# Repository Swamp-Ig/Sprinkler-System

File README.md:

# 6-Zone WiFi Sprinkler Controller

A custom PCB for controlling up to six 24 VAC irrigation solenoid valves via WiFi, using an ESP32 and ESPHome with native Home Assistant integration.

## Features

- **6 independent zones** — each zone switches a 24 VAC solenoid valve via an Omron G5LE-1 relay
- **WiFi control** — ESP32-WROOM-32U with external U.FL antenna connector
- **Home Assistant integration** — ESPHome firmware; zones appear as switch entities
- **Onboard power supply** — HLK-PM01 AC-DC module (mains → 5 V); AMS1117-3.3 regulator (5 V → 3.3 V for ESP32)
- **Relay isolation** — ULN2803A Darlington array isolates ESP32 GPIOs from relay coil drive current
- **Protected design** — varistors on each zone output and across the mains input and transformer primary (RV1/RV2), time-delay fuses on the mains and 24 VAC supplies, per-zone RC snubbers, and an optocoupler-isolated 24 VAC rail sense

## ⚠️ Safety

> **This board carries mains voltage (Line and Neutral) on the PCB.**  
> The HLK-PM01 module is connected directly to mains. The 24 VAC solenoid rail is transformer-isolated but still carries AC voltage.

- Do **not** touch or probe the board while it is powered.
- The enclosure **must** be non-conductive and fully closed before applying mains power.
- All mains wiring must comply with local electrical codes. Use appropriately rated cable and terminals.
- The external transformer must be safety-rated (UL, CE, or equivalent) for your locale.
- Replace fuses only with the specified ratings — see the BOM below.

See [Assembly Notes](docs/assembly.md) for enclosure requirements and conformal coating instructions.

## How It Works

The controller has three linked paths: logic power, 24 VAC valve power, and relay control.

**Logic power:** Mains → F1 → HLK-PM01 → 5 V → AMS1117-3.3 → 3.3 V → ESP32 + logic

**24 VAC path:** Mains → F1 → G3MB-202P SSR (K1, GPIO16) → J2 → external transformer → J3 → F2 → zone relays (K20–K25) → solenoids

**Control:** ESP32 GPIO17–23 → ULN2803A → relay coils K20–K25 → zone outputs J20–J25

When a zone is activated, the ESP32 first enables the 24 VAC rail (K1), then drives the selected relay through the ULN2803A. The ULN2803A acts as a low-side driver, keeping ESP32 GPIO current low while switching the 24 VAC solenoid load through the relay contacts.

## Bill of Materials

| Ref | Component | Value / Part No. | Notes |
|-----|-----------|-----------------|-------|
| U4 | ESP32 module | ESP32-WROOM-32U | External antenna (U.FL) |
| U3 | AC-DC module | HLK-PM01 | 100–240 VAC in, 5 V / 600 mA out |
| U1 | LDO regulator | AMS1117-3.3 | SOT-223 |
| U2 | Optocoupler | EL817 | Isolates the 24 VAC rail sense |
| U5 | Darlington array | ULN2803A | SOIC-18 |
| K1 | Solid-state relay | Omron G3MB-202P | Gates the 24 VAC solenoid rail (GPIO16) |
| K20–K25 | Relay ×6 | Omron G5LE-1 | SPDT, 5 V coil, 10 A / 250 VAC contacts |
| RV20–RV25 | Varistor ×6 | 68 V | Surge protection, one per zone output |
| RV1 | Varistor | 10D471K (275 VAC) | Across mains L–N input, after F1 |
| RV2 | Varistor | 10D471K (275 VAC) | Across K1 SSR output / transformer primary |
| F1 | Fuse | **T1A** (time-delay) | Mains supply — slow-blow for transformer/HLK inrush |
| F2 | Fuse | **T2A** (time-delay) | 24 VAC supply — slow-blow for solenoid inrush |
| D1 | Diode | 1N4148 (0805) | 24 VAC rail sense |
| C5 | Capacitor | 220 µF / ≥10 V | 5 V rail bulk reservoir (THT radial) |
| C1, C7 | SMD capacitors | 10 µF | Supply filtering |
| C2, C3 | SMD capacitors | 22 µF | Supply filtering / sense |
| C4, C6, C20–C25 | SMD capacitors | 100 nF | ESP32 VDD (C4), EN reset (C6), zone snubbers (C20–C25) |
| R1, R3, R5, R6, R8, R10, R11 | SMD resistors | 10 kΩ | Sense, pull-ups, pull-downs |
| R2, R9, R12–R14 | SMD resistors | 4.7 kΩ | Sense, LED series, I²C pull-ups |
| R4, R7 | SMD resistors | 470 Ω | EN/BOOT switch series |
| R20–R25 | SMD resistors | 100 Ω | Zone snubber series |
| LED1, LED2 | LED ×2 | 0805 | IO2 status / power |
| SW1, SW2 | Tactile switch ×2 | — | EN (reset) / BOOT |
| J1 | Screw terminal | Phoenix PT 1,5/3-5.0 (3-pin, 5.0 mm) | Mains input — must be mains-rated |
| J2 | Screw terminal | 2-pin, 5.0 mm | 240 VAC output to transformer primary |
| J3, J20–J25 | Pluggable terminal ×7 | KF2EDG-style, 2-pin | 24 VAC — J3 transformer in, J20–J25 zone outputs |
| XFMR | Transformer (external) | 240 VAC → 24 VAC, ≥50 VA, safety-rated | Size for zones × ~8 VA each |

See [`manufacturing/bom/bom.csv`](manufacturing/bom/bom.csv) for the full BOM with quantities and footprints.

## Reference

- [Wiring & GPIO](docs/wiring.md) — connector pinouts and GPIO assignments
- [ESPHome Configuration](docs/esphome.md) — full firmware config, fault detection, and optional pump relay setup
- [Assembly Notes](docs/assembly.md) — step-by-step build and commissioning guide

## Project Structure

```
Sprinkler System.kicad_pro    ← KiCad project file
Sprinkler System.kicad_sch    ← Schematic
Sprinkler System.kicad_pcb    ← PCB layout
Sprinkler System.pretty/      ← Custom footprints and 3D models
symbols/                       ← Custom symbol library (G3MB-202P)
manufacturing/
  gerbers/                     ← Gerber files for PCB fabrication
  drill/                       ← Excellon drill files
  pos/                         ← Pick-and-place centroid files
  bom/bom.csv                  ← Bill of materials
docs/
  schematic.pdf                ← Schematic PDF
  pcb.pdf                      ← PCB layer PDF
  board.step                   ← 3D STEP model
  wiring.md                    ← Connector and GPIO reference
  esphome.md                   ← ESPHome firmware configuration
  assembly.md                  ← Build and commissioning guide
.githooks/pre-commit           ← Auto-exports fabrication outputs on commit
setup / setup.ps1              ← One-time dev environment setup
release / release.ps1          ← Tag a release version
```

## Developing

### First-time setup

```powershell
.\setup.ps1
```

Configures the git hook path and verifies `kicad-cli` is available. Use `./setup` in Git Bash / WSL.

### Fabrication exports

Gerbers, drill files, PDFs, BOM, netlist, and STEP are regenerated automatically by the pre-commit hook whenever `Sprinkler System.kicad_pcb` or `Sprinkler System.kicad_sch` are staged. No manual export step is needed.

Run DRC and ERC from within KiCad before committing — fix all errors before submitting to a board house.

### Releasing

```powershell
.\release.ps1 v1.1.0
```

Stamps the schematic and PCB title blocks with the version and date, commits (triggering a fresh fabrication export), and creates the git tag. Use `./release v1.1.0` in Git Bash / WSL. Then push:

```powershell
git push && git push origin v1.1.0
```

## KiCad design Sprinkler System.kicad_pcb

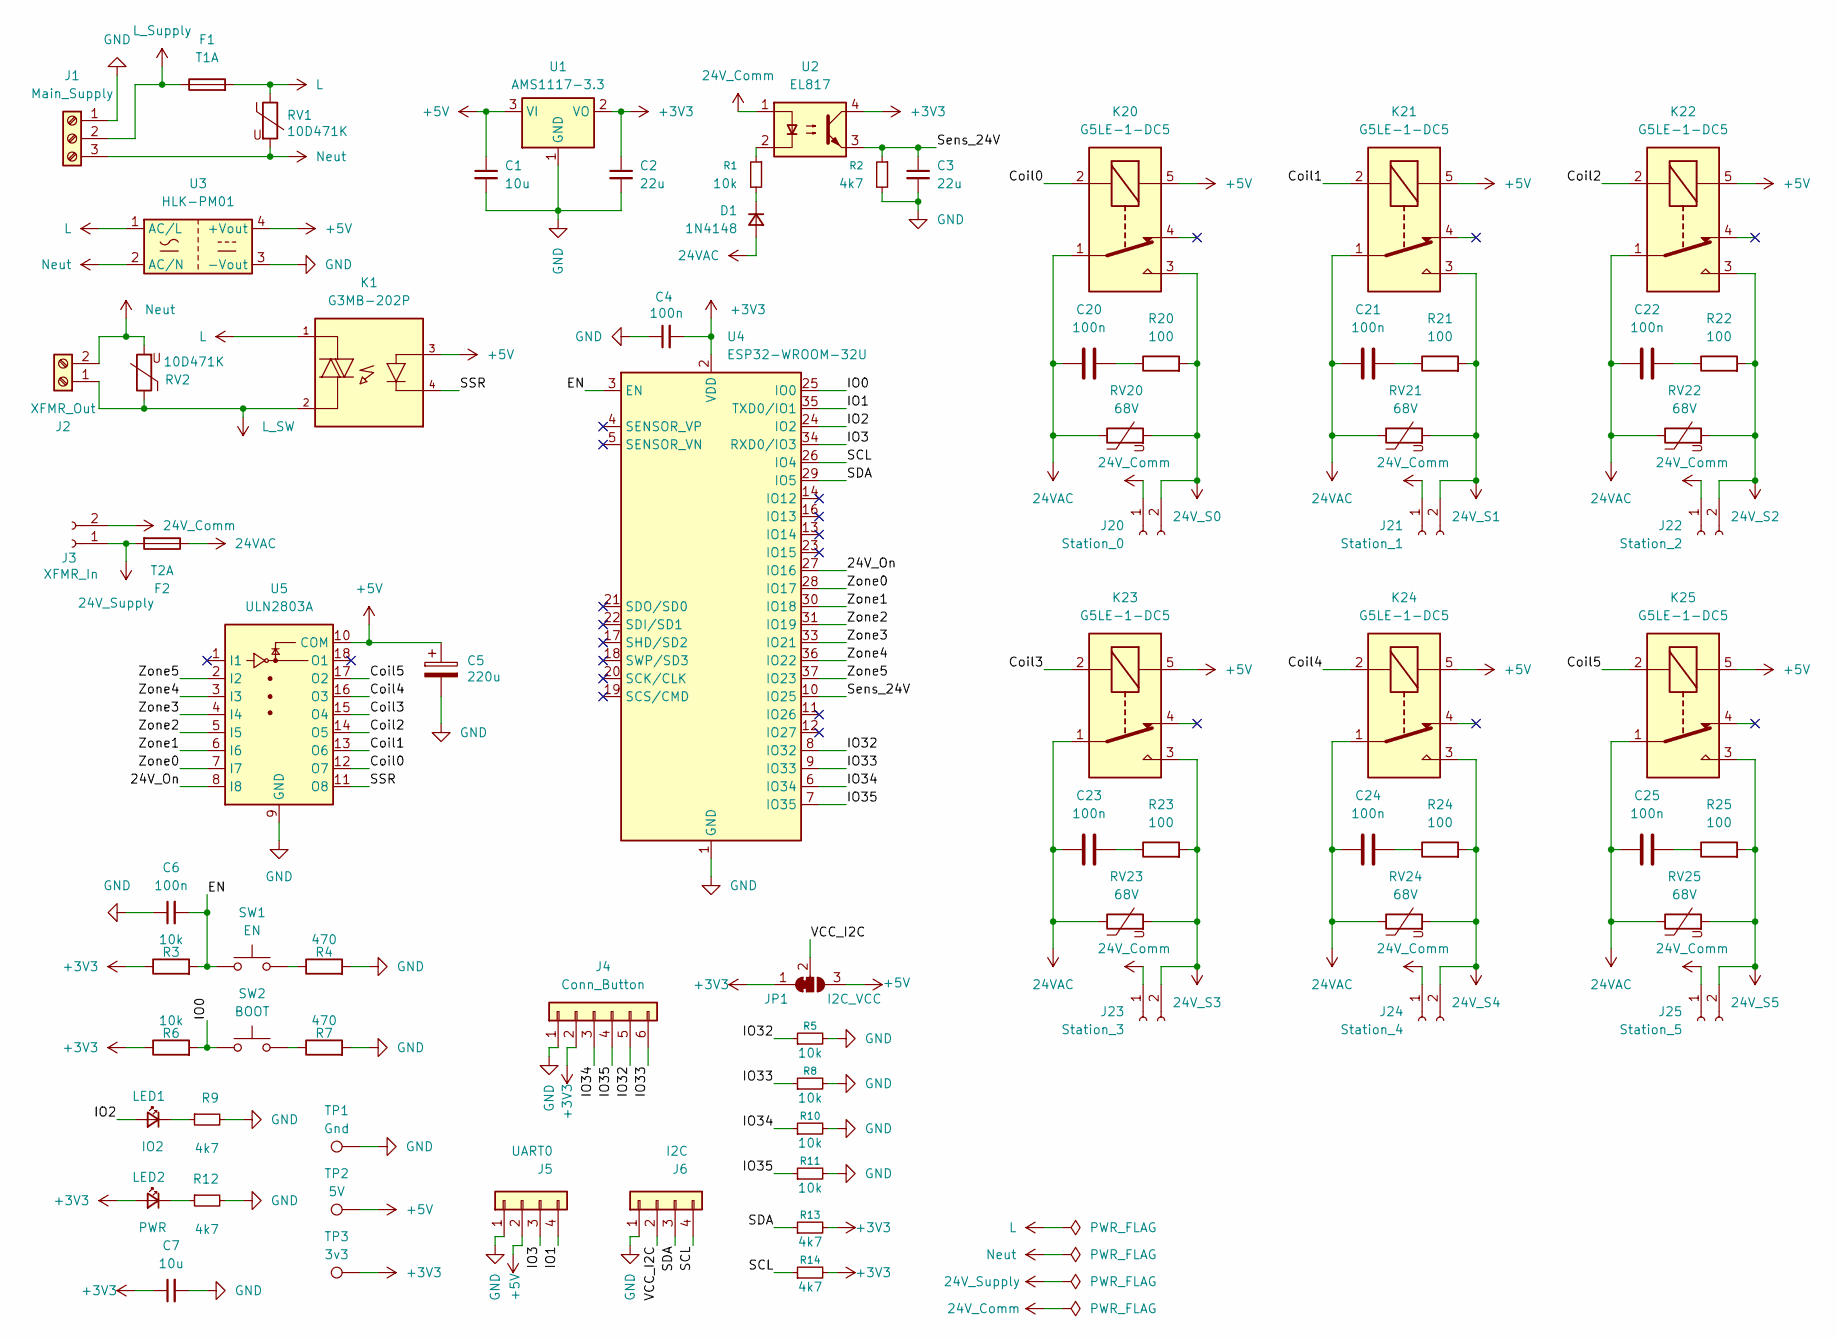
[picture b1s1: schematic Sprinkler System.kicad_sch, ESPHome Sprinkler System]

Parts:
C1, C7: 10u; C_0805_2012Metric_Pad1.18x1.45mm_HandSolder
C2, C3: 22u; C_0805_2012Metric_Pad1.18x1.45mm_HandSolder
C4, C6, C20, C21, C22, C23, C24, C25: 100n; C_0805_2012Metric_Pad1.18x1.45mm_HandSolder
C5: 220u; CP_Radial_D6.3mm_P2.50mm
D1: 1N4148; D_0805_2012Metric_Pad1.15x1.40mm_HandSolder
F1: T1A; Fuseholder_5x20mm_15mm_Pins
F2: T2A; Fuseholder_5x20mm_15mm_Pins
J1: Main_Supply; TerminalBlock_Phoenix_PT-1,5-3-5.0-H_1x03_P5.00mm_Horizontal
J2: XFMR_Out; TerminalBlock_Phoenix_PT-1,5-2-5.0-H_1x02_P5.00mm_Horizontal
J3: XFMR_In; PhoenixContact_MC_1,5_2-G-3.81_1x02_P3.81mm_Horizontal
J4: Conn_Button; JST_XH_B6B-XH-A_1x06_P2.50mm_Vertical
J5: UART0; JST_XH_B4B-XH-A_1x04_P2.50mm_Vertical
J6: I2C; JST_XH_B4B-XH-A_1x04_P2.50mm_Vertical
J20: Station_0; PhoenixContact_MC_1,5_2-G-3.81_1x02_P3.81mm_Horizontal
J21: Station_1; PhoenixContact_MC_1,5_2-G-3.81_1x02_P3.81mm_Horizontal
J22: Station_2; PhoenixContact_MC_1,5_2-G-3.81_1x02_P3.81mm_Horizontal
J23: Station_3; PhoenixContact_MC_1,5_2-G-3.81_1x02_P3.81mm_Horizontal
J24: Station_4; PhoenixContact_MC_1,5_2-G-3.81_1x02_P3.81mm_Horizontal
J25: Station_5; PhoenixContact_MC_1,5_2-G-3.81_1x02_P3.81mm_Horizontal
JP1: I2C_VCC; SolderJumper-3_P1.3mm_Bridged12_RoundedPad1.0x1.5mm_NumberL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
K1: G3MB-202P; RELAY_G3MB-202P; PARTREV 06/09
K20, K21, K22, K23, K24, K25: G5LE-1-DC5; Relay_SPDT_Omron-G5LE-1
LED1: IO2; LED_0805_2012Metric_Pad1.15x1.40mm_HandSolder
LED2: PWR; LED_0805_2012Metric_Pad1.15x1.40mm_HandSolder
R1, R3, R5, R6, R8, R10, R11: 10k; R_0805_2012Metric_Pad1.20x1.40mm_HandSolder
R2, R9, R12, R13, R14: 4k7; R_0805_2012Metric_Pad1.20x1.40mm_HandSolder
R4, R7: 470; R_0805_2012Metric_Pad1.20x1.40mm_HandSolder
R20, R21, R22, R23, R24, R25: 100; R_0805_2012Metric_Pad1.20x1.40mm_HandSolder
RV1, RV2: 10D471K; RV_Disc_D12mm_W4mm_P7.5mm
RV20, RV21, RV22, RV23, RV24, RV25: 68V; RV_Disc_D15.5mm_W5.4mm_P7.5mm
SW1: EN; SW_Push_SPST_NO_Alps_SKRK
SW2: BOOT; SW_Push_SPST_NO_Alps_SKRK
TP1: Gnd; TestPoint_Pad_D1.5mm
TP2: 5V; TestPoint_Pad_D1.5mm
TP3: 3v3; TestPoint_Pad_D1.5mm
U1: AMS1117-3.3; SOT-223-3_TabPin2
U2: EL817; SOP-4_3.8x4.1mm_P2.54mm
U3: HLK-PM01; Converter_ACDC_Hi-Link_HLK-PMxx
U4: ESP32-WROOM-32U
U5: ULN2803A; SOIC-18W_7.5x11.6mm_P1.27mm

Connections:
24VAC: C20.1, C21.1, C22.1, C23.1, C24.1, C25.1, D1.2 (A), F2.1, K20.1, K21.1, K22.1, K23.1, K24.1, K25.1, RV20.1, RV21.1, RV22.1, RV23.1, RV24.1, RV25.1
24V_Comm: J3.2, J20.1, J21.1, J22.1, J23.1, J24.1, J25.1, U2.1
24V_S0: J20.2, K20.3, R20.2, RV20.2
24V_S1: J21.2, K21.3, R21.2, RV21.2
24V_S2: J22.2, K22.3, R22.2, RV22.2
24V_S3: J23.2, K23.3, R23.2, RV23.2
24V_S4: J24.2, K24.3, R24.2, RV24.2
24V_S5: J25.2, K25.3, R25.2, RV25.2
24V_Supply: F2.2, J3.1
+3V3: C2.1, C4.2, C7.1, J4.2, JP1.1 (A), LED2.2 (A), R3.1, R6.1, R13.2, R14.2, TP3.1 (1_1), U1.2 (VO), U2.4, U4.2 (VDD)
+5V: C1.1, C5.1, J5.2, JP1.3 (B), K1.3, K20.5, K21.5, K22.5, K23.5, K24.5, K25.5, TP2.1 (1_1), U1.3 (VI), U3.4 (+Vout), U5.10 (COM)
/24V_On: U4.27 (IO16), U5.8 (I8)
/Coil0: K20.2, U5.12 (O7)
/Coil1: K21.2, U5.13 (O6)
/Coil2: K22.2, U5.14 (O5)
/Coil3: K23.2, U5.15 (O4)
/Coil4: K24.2, U5.16 (O3)
/Coil5: K25.2, U5.17 (O2)
/EN: C6.2, R3.2, SW1.1, U4.3 (EN)
/IO0: R6.2, SW2.1, U4.25 (IO0)
/IO1: J5.4, U4.35 (TXD0/IO1)
/IO2: LED1.2 (A), U4.24 (IO2)
/IO3: J5.3, U4.34 (RXD0/IO3)
/IO32: J4.5, R5.1, U4.8 (IO32)
/IO33: J4.6, R8.1, U4.9 (IO33)
/IO34: J4.3, R10.1, U4.6 (IO34)
/IO35: J4.4, R11.1, U4.7 (IO35)
/SCL: J6.4, R14.1, U4.26 (IO4)
/SDA: J6.3, R13.1, U4.29 (IO5)
/SSR: K1.4, U5.11 (O8)
/Sens_24V: C3.1, R2.1, U2.3, U4.10 (IO25)
/VCC_I2C: J6.2, JP1.2 (C)
/Zone0: U4.28 (IO17), U5.7 (I7)
/Zone1: U4.30 (IO18), U5.6 (I6)
/Zone2: U4.31 (IO19), U5.5 (I5)
/Zone3: U4.33 (IO21), U5.4 (I4)
/Zone4: U4.36 (IO22), U5.3 (I3)
/Zone5: U4.37 (IO23), U5.2 (I2)
GND: C1.2, C2.2, C3.2, C4.1, C5.2, C6.1, C7.2, J1.1, J4.1, J5.1, J6.1, R2.2, R4.2, R5.2, R7.2, R8.2, R9.2, R10.2, R11.2, R12.2, TP1.1 (1_1), U1.1 (GND), U3.3 (-Vout), U4.1 (GND), U4.15 (GND), U4.38 (GND), U4.39 (GND), U5.9 (GND)
L: F1.2, K1.1, RV1.1, U3.1 (AC/L)
L_SW: J2.1, K1.2, RV2.1
L_Supply: F1.1, J1.2
unnamed: C20.2, R20.1
unnamed: C21.2, R21.1
unnamed: C22.2, R22.1
unnamed: C23.2, R23.1
unnamed: C24.2, R24.1
unnamed: C25.2, R25.1
unnamed: D1.1 (K), R1.2
unnamed: LED1.1 (K), R9.1
unnamed: LED2.1 (K), R12.1
unnamed: R1.1, U2.2
unnamed: R4.1, SW1.2
unnamed: R7.1, SW2.2
Neut: J1.3, J2.2, RV1.2, RV2.2, U3.2 (AC/N)

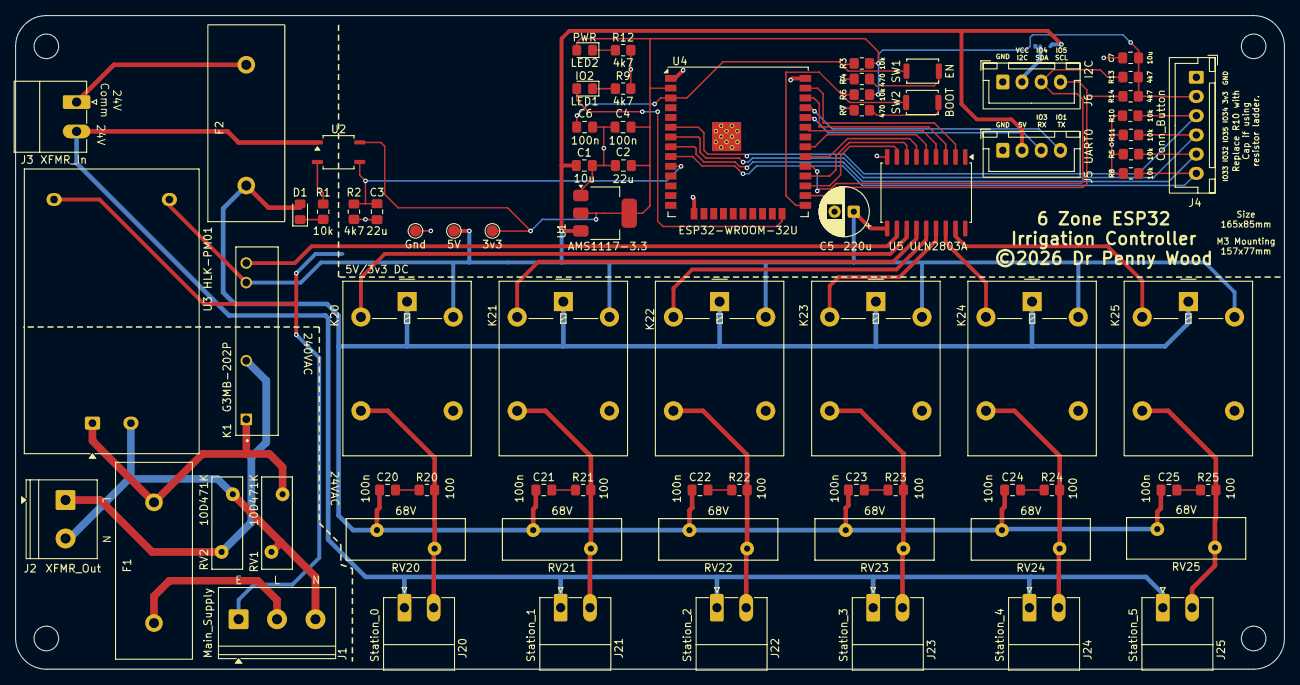
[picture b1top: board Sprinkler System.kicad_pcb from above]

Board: 2 copper layers, 165.0 x 85.0 mm, 80 parts (1 on the bottom side), 55 nets.

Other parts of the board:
H1, H2, H3, H4: MountingHole_3.2mm_M3_ISO7380

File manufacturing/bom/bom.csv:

"Refs","Value","Footprint","Qty","DNP"
"C1","10u","Capacitor_SMD:C_0805_2012Metric_Pad1.18x1.45mm_HandSolder","1",""
"C2","22u","Capacitor_SMD:C_0805_2012Metric_Pad1.18x1.45mm_HandSolder","1",""
"C3","22u","Capacitor_SMD:C_0805_2012Metric_Pad1.18x1.45mm_HandSolder","1",""
"C4","100n","Capacitor_SMD:C_0805_2012Metric_Pad1.18x1.45mm_HandSolder","1",""
"C5","220u","Capacitor_THT:CP_Radial_D6.3mm_P2.50mm","1",""
"C6","100n","Capacitor_SMD:C_0805_2012Metric_Pad1.18x1.45mm_HandSolder","1",""
"C7","10u","Capacitor_SMD:C_0805_2012Metric_Pad1.18x1.45mm_HandSolder","1",""
"C20","100n","Capacitor_SMD:C_0805_2012Metric_Pad1.18x1.45mm_HandSolder","1",""
"C21","100n","Capacitor_SMD:C_0805_2012Metric_Pad1.18x1.45mm_HandSolder","1",""
"C22","100n","Capacitor_SMD:C_0805_2012Metric_Pad1.18x1.45mm_HandSolder","1",""
"C23","100n","Capacitor_SMD:C_0805_2012Metric_Pad1.18x1.45mm_HandSolder","1",""
"C24","100n","Capacitor_SMD:C_0805_2012Metric_Pad1.18x1.45mm_HandSolder","1",""
"C25","100n","Capacitor_SMD:C_0805_2012Metric_Pad1.18x1.45mm_HandSolder","1",""
"D1","1N4148","Diode_SMD:D_0805_2012Metric_Pad1.15x1.40mm_HandSolder","1",""
"F1","T1A","Sprinkler System:Fuseholder_5x20mm_15mm_Pins","1",""
"F2","T2A","Sprinkler System:Fuseholder_5x20mm_15mm_Pins","1",""
"J1","Main_Supply","TerminalBlock_Phoenix:TerminalBlock_Phoenix_PT-1,5-3-5.0-H_1x03_P5.00mm_Horizontal","1",""
"J2","XFMR_Out","TerminalBlock_Phoenix:TerminalBlock_Phoenix_PT-1,5-2-5.0-H_1x02_P5.00mm_Horizontal","1",""
"J3","XFMR_In","Connector_Phoenix_MC:PhoenixContact_MC_1,5_2-G-3.81_1x02_P3.81mm_Horizontal","1",""
"J4","Conn_Button","Connector_JST:JST_XH_B6B-XH-A_1x06_P2.50mm_Vertical","1",""
"J5","UART0","Connector_JST:JST_XH_B4B-XH-A_1x04_P2.50mm_Vertical","1",""
"J6","I2C","Connector_JST:JST_XH_B4B-XH-A_1x04_P2.50mm_Vertical","1",""
"J20","Station_0","Connector_Phoenix_MC:PhoenixContact_MC_1,5_2-G-3.81_1x02_P3.81mm_Horizontal","1",""
"J21","Station_1","Connector_Phoenix_MC:PhoenixContact_MC_1,5_2-G-3.81_1x02_P3.81mm_Horizontal","1",""
"J22","Station_2","Connector_Phoenix_MC:PhoenixContact_MC_1,5_2-G-3.81_1x02_P3.81mm_Horizontal","1",""
"J23","Station_3","Connector_Phoenix_MC:PhoenixContact_MC_1,5_2-G-3.81_1x02_P3.81mm_Horizontal","1",""
"J24","Station_4","Connector_Phoenix_MC:PhoenixContact_MC_1,5_2-G-3.81_1x02_P3.81mm_Horizontal","1",""
"J25","Station_5","Connector_Phoenix_MC:PhoenixContact_MC_1,5_2-G-3.81_1x02_P3.81mm_Horizontal","1",""
"JP1","I2C_VCC","Jumper:SolderJumper-3_P1.3mm_Bridged12_RoundedPad1.0x1.5mm_NumberLabels","1",""
"K1","G3MB-202P","Sprinkler System:RELAY_G3MB-202P","1",""
"K20","G5LE-1-DC5","Relay_THT:Relay_SPDT_Omron-G5LE-1","1",""
"K21","G5LE-1-DC5","Relay_THT:Relay_SPDT_Omron-G5LE-1","1",""
"K22","G5LE-1-DC5","Relay_THT:Relay_SPDT_Omron-G5LE-1","1",""
"K23","G5LE-1-DC5","Relay_THT:Relay_SPDT_Omron-G5LE-1","1",""
"K24","G5LE-1-DC5","Relay_THT:Relay_SPDT_Omron-G5LE-1","1",""
"K25","G5LE-1-DC5","Relay_THT:Relay_SPDT_Omron-G5LE-1","1",""
"LED1","IO2","LED_SMD:LED_0805_2012Metric_Pad1.15x1.40mm_HandSolder","1",""
"LED2","PWR","LED_SMD:LED_0805_2012Metric_Pad1.15x1.40mm_HandSolder","1",""
"R1","10k","Resistor_SMD:R_0805_2012Metric_Pad1.20x1.40mm_HandSolder","1",""
"R2","4k7","Resistor_SMD:R_0805_2012Metric_Pad1.20x1.40mm_HandSolder","1",""
"R3","10k","Resistor_SMD:R_0805_2012Metric_Pad1.20x1.40mm_HandSolder","1",""
"R4","470","Resistor_SMD:R_0805_2012Metric_Pad1.20x1.40mm_HandSolder","1",""
"R5","10k","Resistor_SMD:R_0805_2012Metric_Pad1.20x1.40mm_HandSolder","1",""
"R6","10k","Resistor_SMD:R_0805_2012Metric_Pad1.20x1.40mm_HandSolder","1",""
"R7","470","Resistor_SMD:R_0805_2012Metric_Pad1.20x1.40mm_HandSolder","1",""
"R8","10k","Resistor_SMD:R_0805_2012Metric_Pad1.20x1.40mm_HandSolder","1",""
"R9","4k7","Resistor_SMD:R_0805_2012Metric_Pad1.20x1.40mm_HandSolder","1",""
"R10","10k","Resistor_SMD:R_0805_2012Metric_Pad1.20x1.40mm_HandSolder","1",""
"R11","10k","Resistor_SMD:R_0805_2012Metric_Pad1.20x1.40mm_HandSolder","1",""
"R12","4k7","Resistor_SMD:R_0805_2012Metric_Pad1.20x1.40mm_HandSolder","1",""
"R13","4k7","Resistor_SMD:R_0805_2012Metric_Pad1.20x1.40mm_HandSolder","1",""
"R14","4k7","Resistor_SMD:R_0805_2012Metric_Pad1.20x1.40mm_HandSolder","1",""
"R20","100","Resistor_SMD:R_0805_2012Metric_Pad1.20x1.40mm_HandSolder","1",""
"R21","100","Resistor_SMD:R_0805_2012Metric_Pad1.20x1.40mm_HandSolder","1",""
"R22","100","Resistor_SMD:R_0805_2012Metric_Pad1.20x1.40mm_HandSolder","1",""
"R23","100","Resistor_SMD:R_0805_2012Metric_Pad1.20x1.40mm_HandSolder","1",""
"R24","100","Resistor_SMD:R_0805_2012Metric_Pad1.20x1.40mm_HandSolder","1",""
"R25","100","Resistor_SMD:R_0805_2012Metric_Pad1.20x1.40mm_HandSolder","1",""
"RV1","10D471K","Varistor:RV_Disc_D12mm_W4mm_P7.5mm","1",""
"RV2","10D471K","Varistor:RV_Disc_D12mm_W4mm_P7.5mm","1",""
"RV20","68V","Varistor:RV_Disc_D15.5mm_W5.4mm_P7.5mm","1",""
"RV21","68V","Varistor:RV_Disc_D15.5mm_W5.4mm_P7.5mm","1",""
"RV22","68V","Varistor:RV_Disc_D15.5mm_W5.4mm_P7.5mm","1",""
"RV23","68V","Varistor:RV_Disc_D15.5mm_W5.4mm_P7.5mm","1",""
"RV24","68V","Varistor:RV_Disc_D15.5mm_W5.4mm_P7.5mm","1",""
"RV25","68V","Varistor:RV_Disc_D15.5mm_W5.4mm_P7.5mm","1",""
"SW1","EN","Button_Switch_SMD:SW_Push_SPST_NO_Alps_SKRK","1",""
"SW2","BOOT","Button_Switch_SMD:SW_Push_SPST_NO_Alps_SKRK","1",""
"TP1","Gnd","TestPoint:TestPoint_Pad_D1.5mm","1",""
"TP2","5V","TestPoint:TestPoint_Pad_D1.5mm","1",""
"TP3","3v3","TestPoint:TestPoint_Pad_D1.5mm","1",""
"U1","AMS1117-3.3","Package_TO_SOT_SMD:SOT-223-3_TabPin2","1",""
"U2","EL817","Package_SO:SOP-4_3.8x4.1mm_P2.54mm","1",""
"U3","HLK-PM01","Converter_ACDC:Converter_ACDC_Hi-Link_HLK-PMxx","1",""
"U4","ESP32-WROOM-32U","RF_Module:ESP32-WROOM-32U","1",""
"U5","ULN2803A","Package_SO:SOIC-18W_7.5x11.6mm_P1.27mm","1",""

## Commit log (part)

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2026-05-10 chore: initial KiCad project template
    - Directory scaffold: sheets, footprints, symbols, 3d_models, manufacturing, docs
    - .gitignore: excludes *.kicad_prl, *-backups/, lock files, fp-info-cache
    - .gitattributes: KiCad S-expression files as text/LF; 3D models as binary
    - .vscode/settings.json: file associations, Explorer filters, kicad.cliPath
    - .vscode/tasks.json: kicad-cli tasks (ERC, DRC, Gerbers, PDF, BOM, STEP, netlist)
    - .vscode/extensions.json: recommended extensions (TOML, Git Graph, GitLens)
2026-05-10 Prepared Spinkler System Baseline
2026-05-24 Ready to Send
2026-05-31 feat: advance 6-zone sprinkler controller design and documentation
    * replace template docs with full project README (safety notes, enclosure guidance, power/control paths, wiring, BOM, GPIO map)
    * update schematic and PCB with major reannotation/layout changes, added test points, and 24 VAC net handling refinements
    * add/update project rule settings (new 24VAC net class, net class priorities, DRC exclusion updates)
    * adjust relay footprint 3D model orientation/offset
2026-06-01 Project tweaks
2026-06-03 Update PCB layout, schematic, and project config
2026-06-03 Manufacturing files ready for sending.
2026-06-26 Release v1.0.0

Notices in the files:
Sprinkler System.kicad_pcb:
©2026 Dr Penny Wood
